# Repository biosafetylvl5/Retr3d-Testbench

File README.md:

# Retr3d Testbench
**Retr3d Testbench**, or just **Testbench** is an Arduino Mega shield build to enable self-testing. It uses resistors to check the current sinking of each pin after it checks if any pins are stuck HIGH or LOW.

## Images

## Origin
**Testbench** was designed to be used in tandem with Retr3d, a framework for designing custom 3D printers to be made out of e-waste. Cheap Arduino Mega clones have a relatively high failure rate, and **Testbench** hopes to find problem boards before they become a problem. With this in mind, certain design choices were made (see **Note 2**) that reflect this origin.

### Notes

##### Note 1:
Pins **0** and **1** are not tested because they must be used to upload the self-testing sketch, and therefore are assumed to be working. 

##### Note 2:

Pin **27** is not tested because it is a pin not utilized in the RAMPS 1.4 3D printer shield and instead is utilized to blink the indicator LED.

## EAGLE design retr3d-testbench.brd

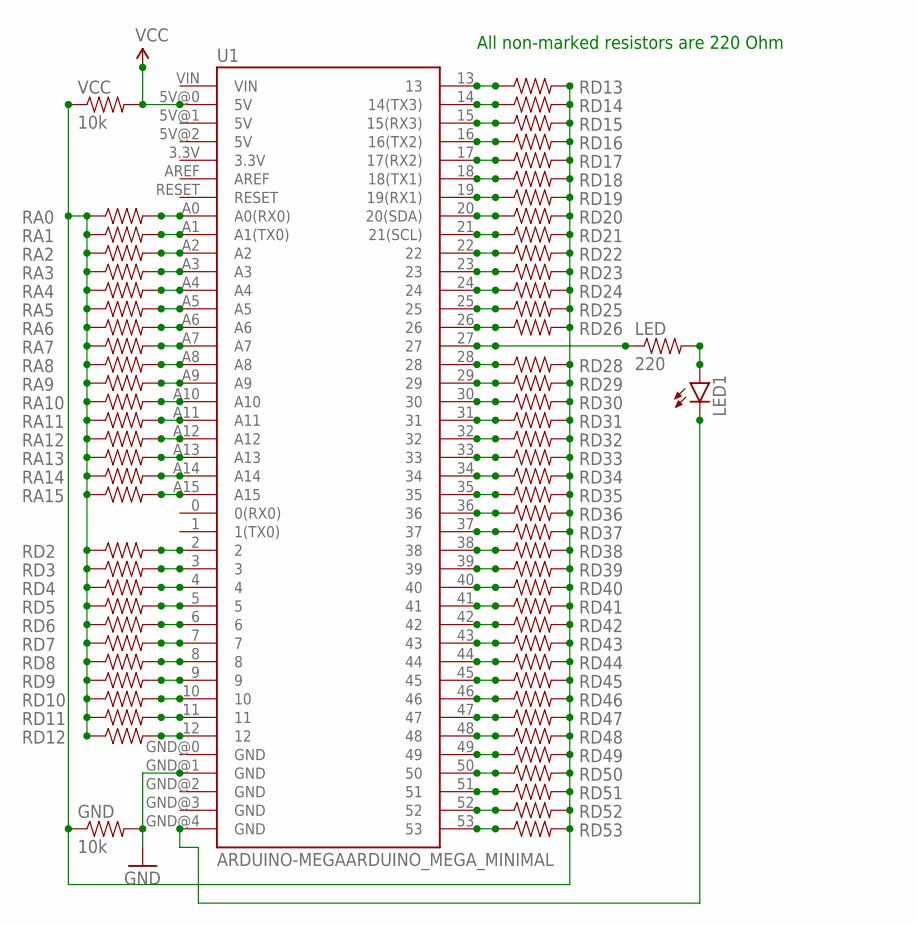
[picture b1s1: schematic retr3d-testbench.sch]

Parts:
GND: 10k; 0805
LED: 220; 0805
LED1: LEDRETR3D; LED-1206-BOTTOM
RA0, RA1, RA2, RA3, RA4, RA5, RA6, RA7, RA8, RA9, RA10, RA11, RA12, RA13, RA14, RA15: 220; 0805
RD2, RD3, RD4, RD5, RD6, RD7, RD8, RD9, RD10, RD11, RD12, RD13, RD14, RD15, RD16, RD17, RD18, RD19, RD20, RD21, RD22, RD23, RD24, RD25, RD26, RD28, RD29, RD30, RD31, RD32, RD33, RD34, RD35, RD36, RD37, RD38, RD39, RD40, RD41, RD42, RD43, RD44, RD45, RD46, RD47, RD48, RD49, RD50, RD51, RD52, RD53: 220; 0805
U1: ARDUINO-MEGAARDUINO_MEGA_MINIMAL; ARDUINO_MEGA
VCC: 10k; 0805

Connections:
unnamed: RD13.1, U1.13
unnamed: LED.1, U1.27
unnamed: RA0.2, U1.A0 (A0(RX0))
unnamed: LED.2, LED1.A
unnamed: RD15.1, U1.15 (15(RX3))
unnamed: RA2.2, U1.A2
unnamed: RA4.2, U1.A4
unnamed: RD17.1, U1.17 (17(RX2))
unnamed: RA6.2, U1.A6
unnamed: RA8.2, U1.A8
unnamed: RD19.1, U1.19 (19(RX1))
unnamed: RA10.2, U1.A10
unnamed: RA11.2, U1.A11
unnamed: RA12.2, U1.A12
unnamed: RA13.2, U1.A13
unnamed: RD21.1, U1.21 (21(SCL))
unnamed: RA14.2, U1.A14
unnamed: RA15.2, U1.A15
unnamed: RD22.1, U1.22
unnamed: RD2.2, U1.2
unnamed: RD3.2, U1.3
unnamed: RD5.2, U1.5
unnamed: RD24.1, U1.24
unnamed: RD4.2, U1.4
unnamed: RD6.2, U1.6
unnamed: RD7.2, U1.7
unnamed: RD9.2, U1.9
unnamed: RD26.1, U1.26
unnamed: RD8.2, U1.8
unnamed: RD10.2, U1.10
unnamed: RD11.2, U1.11
unnamed: RD12.2, U1.12
unnamed: RD28.1, U1.28
unnamed: RD14.1, U1.14 (14(TX3))
unnamed: RD16.1, U1.16 (16(TX2))
unnamed: RD30.1, U1.30
unnamed: RD18.1, U1.18 (18(TX1))
unnamed: RD20.1, U1.20 (20(SDA))
unnamed: RD32.1, U1.32
unnamed: RD23.1, U1.23
unnamed: RD25.1, U1.25
unnamed: RD29.1, U1.29
unnamed: RD31.1, U1.31
unnamed: RD33.1, U1.33
unnamed: RD34.1, U1.34
unnamed: RD38.1, U1.38
unnamed: RD35.1, U1.35
unnamed: RD36.1, U1.36
unnamed: RD37.1, U1.37
unnamed: RD39.1, U1.39
unnamed: RD40.1, U1.40
unnamed: RD41.1, U1.41
unnamed: RD42.1, U1.42
unnamed: RD43.1, U1.43
unnamed: RD44.1, U1.44
unnamed: RD45.1, U1.45
unnamed: RD46.1, U1.46
unnamed: RD47.1, U1.47
unnamed: RD53.1, U1.53
unnamed: RD52.1, U1.52
unnamed: RD51.1, U1.51
unnamed: RD50.1, U1.50
unnamed: RD49.1, U1.49
unnamed: RD48.1, U1.48
unnamed: RA1.2, U1.A1 (A1(TX0))
unnamed: RA3.2, U1.A3
unnamed: RA5.2, U1.A5
unnamed: RA7.2, U1.A7
unnamed: RA9.2, U1.A9
N$TEST: GND.1, RA0.1, RA1.1, RA2.1, RA3.1, RA4.1, RA5.1, RA6.1, RA7.1, RA8.1, RA9.1, RA10.1, RA11.1, RA12.1, RA13.1, RA14.1, RA15.1, RD2.1, RD3.1, RD4.1, RD5.1, RD6.1, RD7.1, RD8.1, RD9.1, RD10.1, RD11.1, RD12.1, RD13.2, RD14.2, RD15.2, RD16.2, RD17.2, RD18.2, RD19.2, RD20.2, RD21.2, RD22.2, RD23.2, RD24.2, RD25.2, RD26.2, RD28.2, RD29.2, RD30.2, RD31.2, RD32.2, RD33.2, RD34.2, RD35.2, RD36.2, RD37.2, RD38.2, RD39.2, RD40.2, RD41.2, RD42.2, RD43.2, RD44.2, RD45.2, RD46.2, RD47.2, RD48.2, RD49.2, RD50.2, RD51.2, RD52.2, RD53.2, VCC.1
VCC: U1.5V@0 (5V), VCC.2

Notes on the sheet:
All non-marked resistors are 220 Ohm

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
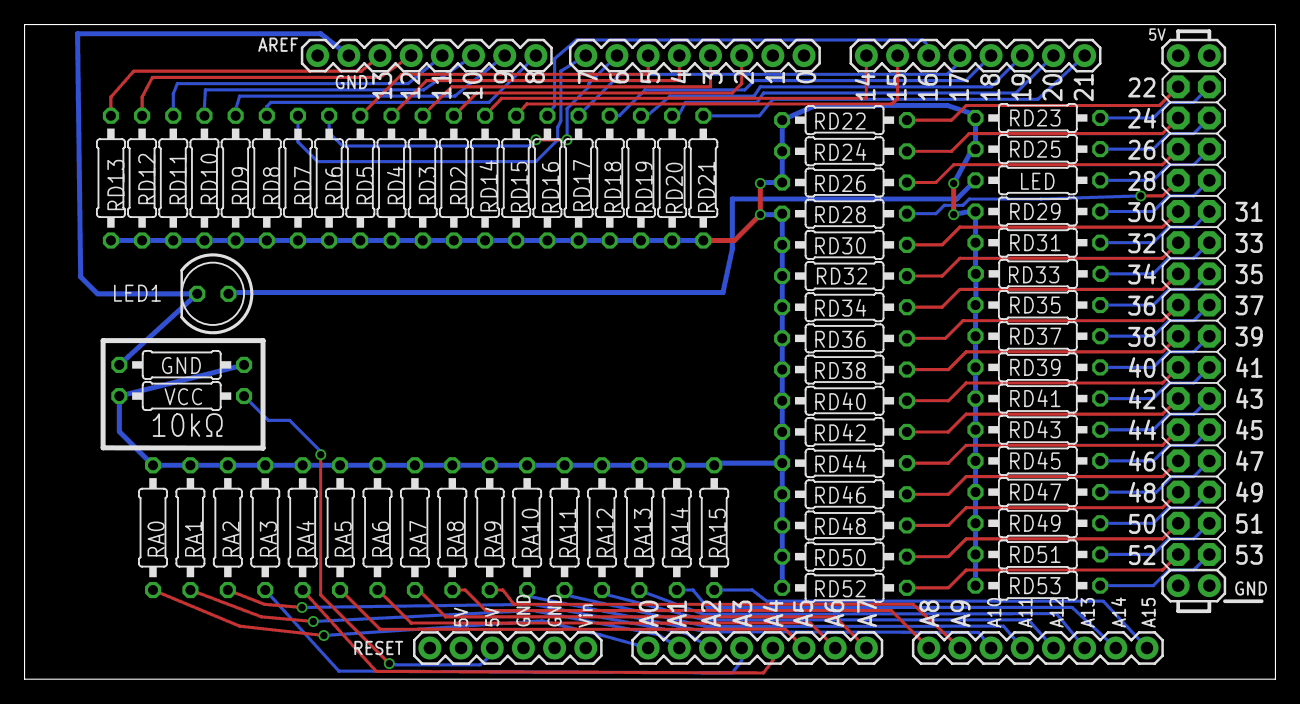
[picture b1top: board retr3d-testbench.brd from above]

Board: 2 copper layers, 101.9 x 53.3 mm, 72 parts (0 on the bottom side), 72 nets.

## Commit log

2015-08-23 README update
2015-08-23 Images Added; README Update
2015-08-23 Added images to README
2015-08-23 Cropped board.png
2015-08-28 Updated docs
2015-08-28 Added SMD one sided version
2015-08-28 Change pictures to SMD
2015-08-28 Routed unrouted trace
2015-08-28 Better Clearence
2015-10-01 Hatched fill for easier soldering
2015-10-01 Hatched polygon for easier soldering
2015-10-03 Redesign for easier fabrication
2015-10-09 Added code
2015-12-07 Fixed a possibility for errors

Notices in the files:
parts and their libraries:
SparkFun-Boards: Licensing: Creative Commons ShareAlike 4.0 International - https://creativecommons.org/licenses/by-sa/4.0
